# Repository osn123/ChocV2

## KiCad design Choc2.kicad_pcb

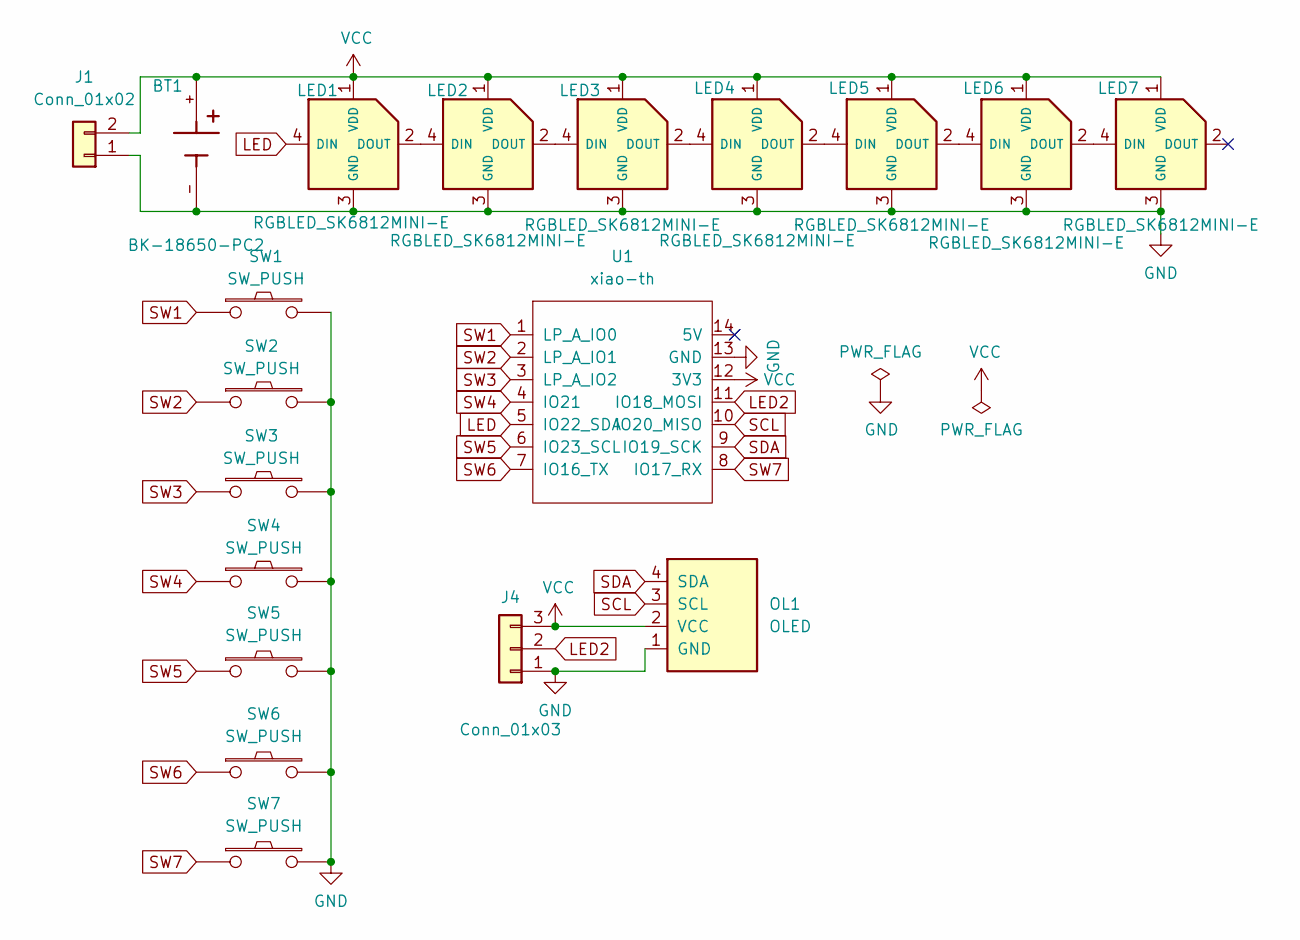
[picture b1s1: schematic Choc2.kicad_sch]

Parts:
BT1: BK-18650-PC2; BAT_BK-18650-PC2; PARTREV F
J1: Conn_01x02; JST_PH_S2B-PH-K_1x02_P2.00mm_Horizontal
J4: Conn_01x03; JST_PH_S3B-PH-K_1x03_P2.00mm_Horizontal
LED1, LED2, LED3, LED4, LED5, LED6, LED7: RGBLED_SK6812MINI-E; SK6812MINI-E-backside3D
OL1: OLED; MODULE_DM-OLED096-636
SW1, SW2, SW3, SW4, SW5, SW6, SW7: SW_PUSH; Choc_v2_Hotswap_1u_16_3D
U1: xiao-th; Micon_XIAO_TH3D

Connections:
GND: BT1.-, J1.1, J4.1, LED1.3 (GND), LED2.3 (GND), LED3.3 (GND), LED4.3 (GND), LED5.3 (GND), LED6.3 (GND), LED7.3 (GND), OL1.1 (GND), SW1.2, SW2.2, SW3.2, SW4.2, SW5.2, SW6.2, SW7.2, U1.13 (GND)
LED: LED1.4 (DIN), U1.5 (IO22_SDA)
LED2: J4.2, U1.11 (IO18_MOSI)
unnamed: LED1.2 (DOUT), LED2.4 (DIN)
unnamed: LED2.2 (DOUT), LED3.4 (DIN)
unnamed: LED3.2 (DOUT), LED4.4 (DIN)
unnamed: LED4.2 (DOUT), LED5.4 (DIN)
unnamed: LED5.2 (DOUT), LED6.4 (DIN)
unnamed: LED6.2 (DOUT), LED7.4 (DIN)
SCL: OL1.3 (SCL), U1.10 (IO20_MISO)
SDA: OL1.4 (SDA), U1.9 (IO19_SCK)
SW1: SW1.1, U1.1 (LP_A_IO0)
SW2: SW2.1, U1.2 (LP_A_IO1)
SW3: SW3.1, U1.3 (LP_A_IO2)
SW4: SW4.1, U1.4 (IO21)
SW5: SW5.1, U1.6 (IO23_SCL)
SW6: SW6.1, U1.7 (IO16_TX)
SW7: SW7.1, U1.8 (IO17_RX)
VCC: BT1.+, J1.2, J4.3, LED1.1 (VDD), LED2.1 (VDD), LED3.1 (VDD), LED4.1 (VDD), LED5.1 (VDD), LED6.1 (VDD), LED7.1 (VDD), OL1.2 (VCC), U1.12 (3V3)

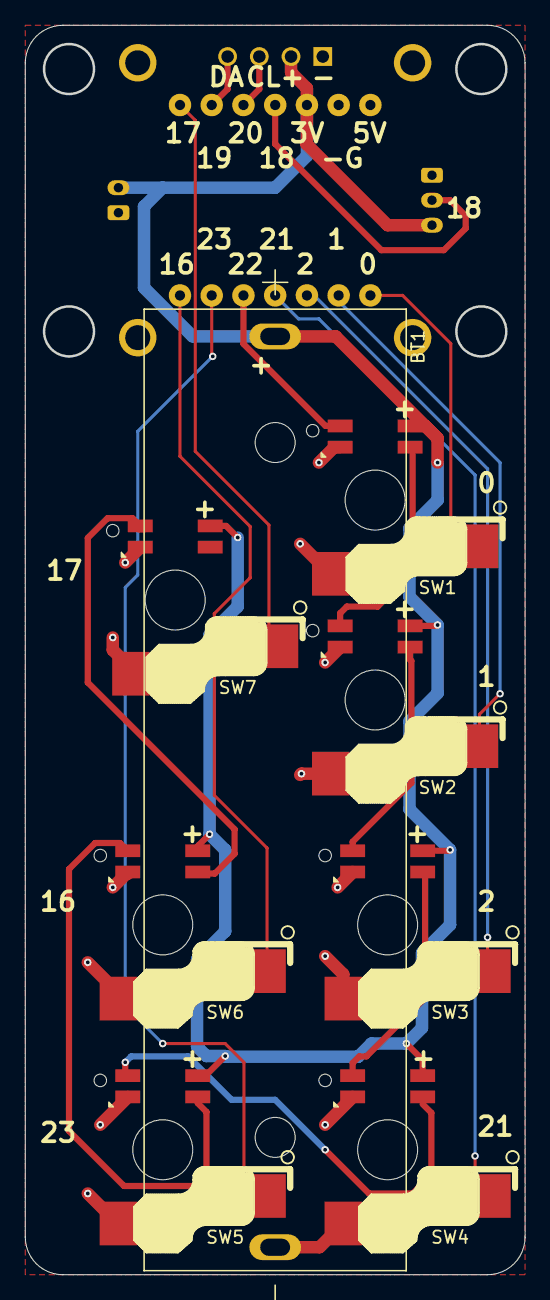
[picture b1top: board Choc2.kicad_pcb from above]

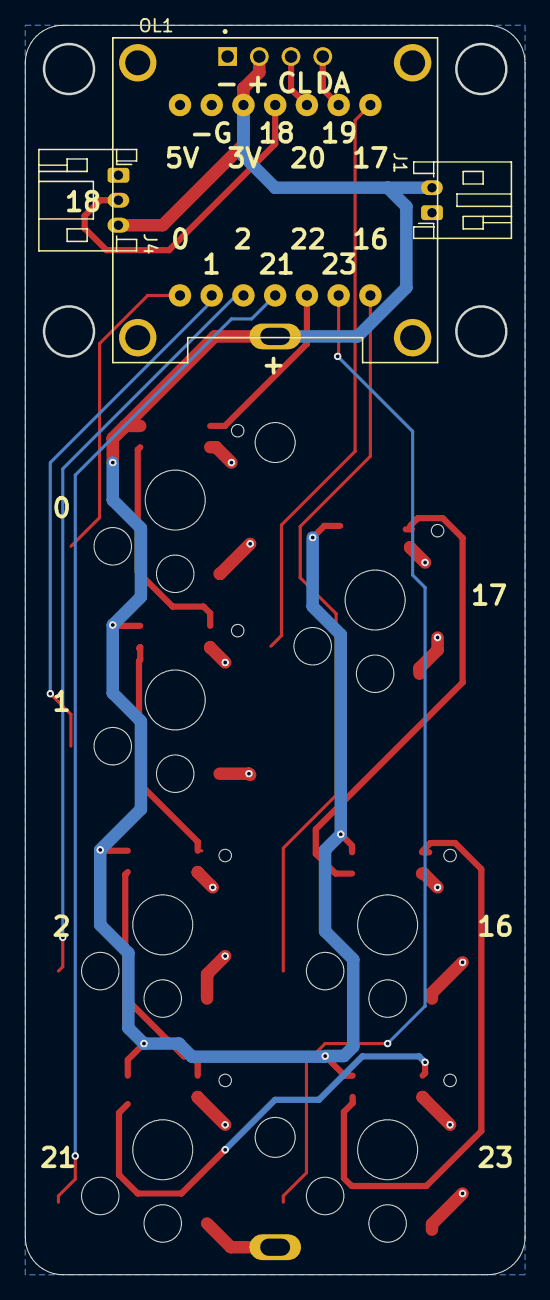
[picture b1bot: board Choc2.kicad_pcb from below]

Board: 2 copper layers, 39.9 x 99.9 mm, 19 parts (3 on the bottom side), 19 nets.

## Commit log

2025-04-08 chipSocket
2025-04-08 ver1
2025-04-08 silk
2025-04-08 holeMove
2025-04-08 Remap
2025-04-09 buyPurple
2025-04-17 composition
